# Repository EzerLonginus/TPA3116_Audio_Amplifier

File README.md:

# TPA3116_Audio_Amplifier
TPA3116 Stereo and Sub-Woofer Audio Amplifier.  D-Class 50W Stereo Amplifier.  The schematic and layout are pretty much similar to the one layout in the datasheet.  Nothing too fancy, however the Subwoofer does have a summed Left and Right channel via two 470 ohm resistors `R78 R79`. The input is assumed to be a line level stereo input through a 3.5mm jack.  However, there are some through hole pins should a different connector or input be desired.  The banana plug holes on the all the speaker ouputs are for potential convenience for swapping out speakers.  Not strictly necessary, one could solder speaker cable to those through holes, or just juse the screw terminals.  The banana plugs for the power input are there for similar reasons.  

## Schematic

## Layout

## BOM Link
1. [OCTOPART BOM](https://octopart.com/bom-tool/Kn64f8nE)

## Datasheets and External Links
1. [TPA3116](https://www.ti.com/lit/ds/symlink/tpa3116d2.pdf)

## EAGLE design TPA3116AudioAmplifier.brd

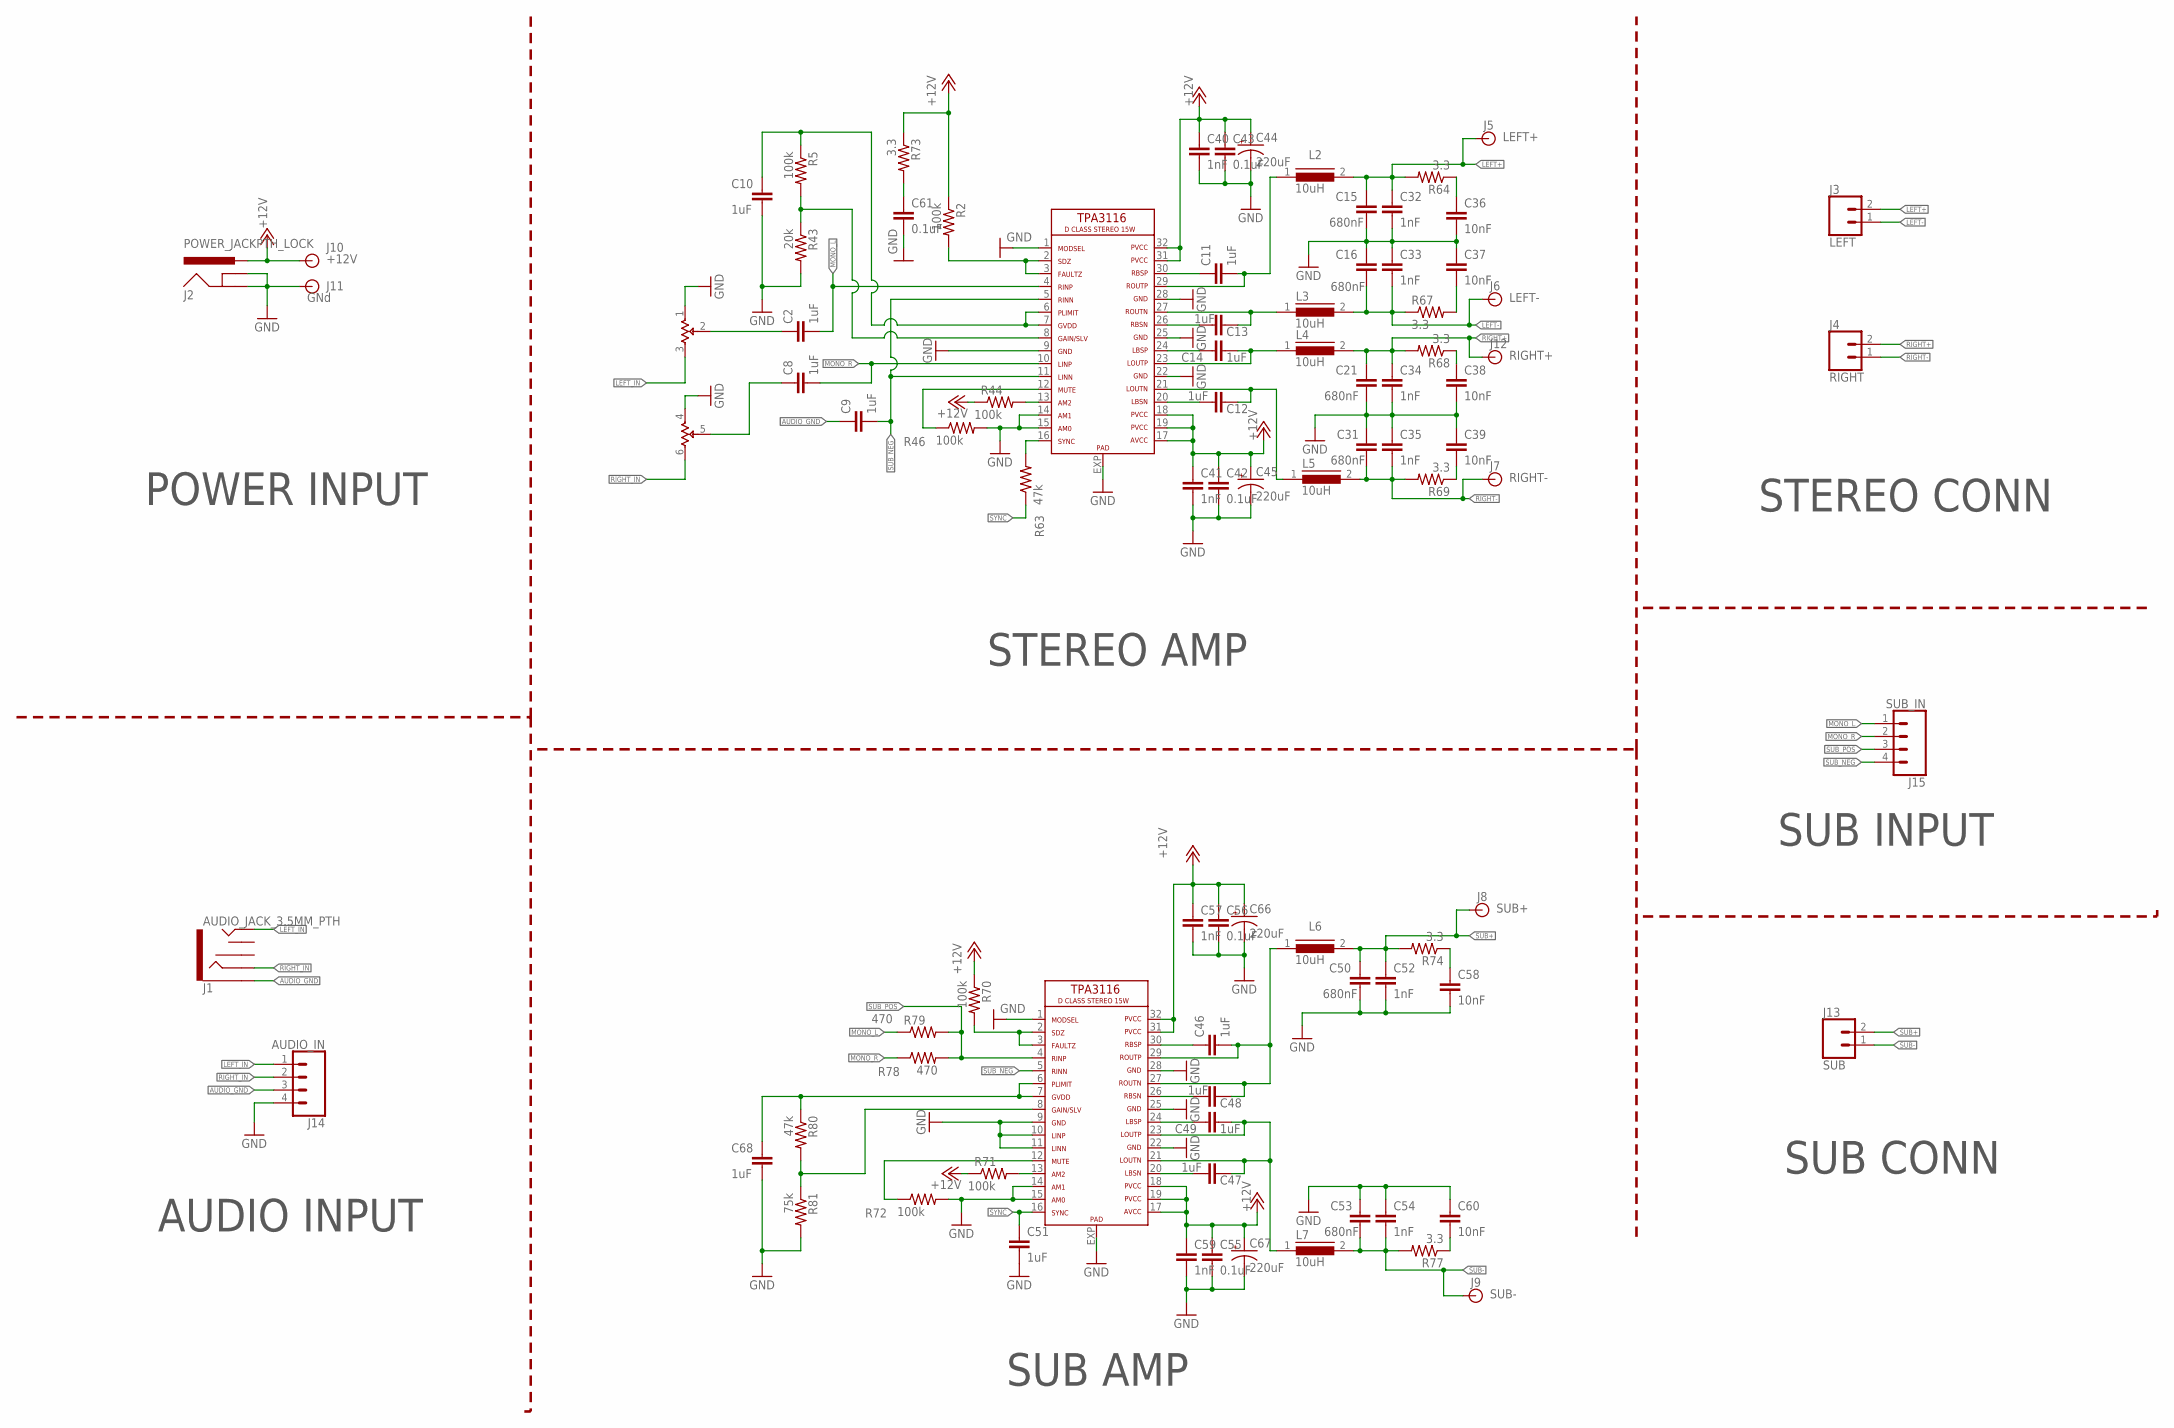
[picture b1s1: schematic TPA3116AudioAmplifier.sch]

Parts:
C2, C8, C9, C10, C11, C12, C13, C14, C46, C47, C48, C49, C51, C68: 1uF; C0603K
C15, C16, C21, C31, C50, C53: 680nF; C0805
C32, C33, C34, C35, C40, C41, C52, C54, C57, C59: 1nF; C0603K
C36, C37, C38, C39, C58, C60: 10nF; C0603K
C42, C43, C55, C56, C61: 0.1uF; C0603K
C44, C45, C66, C67: 220uF; E5-10,5
J1: AUDIO_JACK_3.5MM_PTH; AUDIO-JACK
J2: POWER_JACKPTH_LOCK; POWER_JACK_PTH_LOCK
J3: LEFT; SCREWTERMINAL-5MM-2
J4: RIGHT; SCREWTERMINAL-5MM-2
J5: LEFT+; BANANA_CONN
J6: LEFT-; BANANA_CONN
J7: RIGHT-; BANANA_CONN
J8: SUB+; BANANA_CONN
J9: SUB-; BANANA_CONN
J10: +12V; BANANA_CONN
J11: GNd; BANANA_CONN
J12: RIGHT+; BANANA_CONN
J13: SUB; SCREWTERMINAL-5MM-2
J14: AUDIO_IN; 1X04
J15: SUB_IN; 1X04
L2, L3, L4, L5, L6, L7: 10uH; DR125
R2, R5, R44, R46, R70, R71, R72: 100k; R0805
R43: 20k; R0805
R63, R80: 47k; R0805
R64, R67, R68, R69, R73, R74, R77: 3.3; M0805
R78, R79: 470; R0805
R81: 75k; R0805
U$1, U$3: TPA3116HTSSOP32; HTSSOP32DAP
U$2: DUAL_POT_H

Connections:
+12V: C40.1, C41.1, C42.1, C43.1, C44.+, C45.+, C55.1, C56.1, C57.1, C59.1, C66.+, C67.+, J2.PWR, J10.P$1, R2.1, R44.1, R70.1, R71.1, R73.1, U$1.17 (AVCC), U$1.18 (PVCC0), U$1.19 (PVCC1), U$1.31 (PVCC2), U$1.32 (PVCC3), U$3.17 (AVCC), U$3.18 (PVCC0), U$3.19 (PVCC1), U$3.31 (PVCC2), U$3.32 (PVCC3)
AUDIO_GND: C9.1, J1.SLEEVE, J14.3
GND: C10.2, C15.2, C16.1, C21.2, C31.1, C32.2, C33.1, C34.2, C35.1, C36.2, C37.1, C38.2, C39.1, C40.2, C41.2, C42.2, C43.2, C44.-, C45.-, C50.2, C51.2, C52.2, C53.1, C54.1, C55.2, C56.2, C57.2, C58.2, C59.2, C60.1, C61.2, C66.-, C67.-, C68.2, J2.GND, J2.GNDBREAK, J11.P$1, J14.4, R43.2, R46.2, R72.2, R81.2, U$1.1 (MODSEL), U$1.9 (GND0), U$1.10 (LINP), U$1.11 (LINN), U$1.14 (AM1), U$1.15 (AM0), U$1.22 (GND1), U$1.25 (GND2), U$1.28 (GND3), U$1.EXP, U$2.1, U$2.4, U$3.1 (MODSEL), U$3.9 (GND0), U$3.14 (AM1), U$3.15 (AM0), U$3.22 (GND1), U$3.25 (GND2), U$3.28 (GND3), U$3.EXP
LEFT+: C15.1, C32.1, J3.2, J5.P$1, L2.2, R64.2
LEFT-: C16.2, C33.2, J3.1, J6.P$1, L3.2, R67.1
LEFT_IN: J1.TIP, J14.1, U$2.3
LOUTN: C13.2, L3.1, U$3.27 (ROUTN)
LOUTP: C11.2, L2.1, U$3.29 (ROUTP)
MONO_L: C2.2, J15.1, R79.1, U$3.4 (RINP)
MONO_R: C8.2, J15.2, R78.1, U$3.10 (LINP)
unnamed: C8.1, U$2.5
unnamed: R70.2, U$1.2 (SDZ), U$1.3 (FAULTZ)
unnamed: C61.1, R73.2
unnamed: R2.2, U$3.2 (SDZ), U$3.3 (FAULTZ)
unnamed: R44.2, U$3.13 (AM2)
unnamed: R46.1, U$3.12 (MUTE)
unnamed: R5.2, R43.1, U$3.8 (GAIN/SLV)
unnamed: C2.1, U$2.2
unnamed: R80.2, R81.1, U$1.8 (GAIN/SLV)
unnamed: C10.1, R5.1, U$3.6 (PLIMIT), U$3.7 (GVDD)
unnamed: R63.2, U$3.16 (SYNC)
unnamed: C11.1, U$3.30 (RBSP)
unnamed: C12.1, U$3.20 (LBSN)
unnamed: C13.1, U$3.26 (RBSN)
unnamed: C14.1, U$3.24 (LBSP)
unnamed: C68.1, R80.1, U$1.6 (PLIMIT), U$1.7 (GVDD)
unnamed: R71.2, U$1.13 (AM2)
unnamed: C36.1, R64.1
unnamed: R72.1, U$1.12 (MUTE)
unnamed: C38.1, R68.1
unnamed: C37.2, R67.2
unnamed: C39.2, R69.1
unnamed: C46.1, U$1.30 (RBSP)
unnamed: C47.1, U$1.20 (LBSN)
unnamed: C48.1, U$1.26 (RBSN)
unnamed: C49.1, U$1.24 (LBSP)
unnamed: C58.1, R74.1
unnamed: C60.2, R77.1
RIGHT+: C21.1, C34.1, J4.2, J12.P$1, L4.2, R68.2
RIGHT-: C31.2, C35.2, J4.1, J7.P$1, L5.2, R69.2
RIGHT_IN: J1.RING, J14.2, U$2.6
ROUTN: C12.2, L5.1, U$3.21 (LOUTN)
ROUTP: C14.2, L4.1, U$3.23 (OUTPL)
SOUTN: C47.2, C49.2, L7.1, U$1.21 (LOUTN), U$1.23 (OUTPL)
SOUTP: C46.2, C48.2, L6.1, U$1.27 (ROUTN), U$1.29 (ROUTP)
SUB+: C50.1, C52.1, J8.P$1, J13.2, L6.2, R74.2
SUB-: C53.2, C54.2, J9.P$1, J13.1, L7.2, R77.2
SUB_NEG: C9.2, J15.4, U$1.5 (RINN), U$3.5 (RINN), U$3.11 (LINN)
SUB_POS: J15.3, R78.2, R79.2, U$1.4 (RINP)
SYNC: C51.1, R63.1, U$1.16 (SYNC)

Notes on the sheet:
SUB AMP
STEREO AMP
AUDIO INPUT
POWER INPUT
STEREO CONN
SUB INPUT
SUB CONN

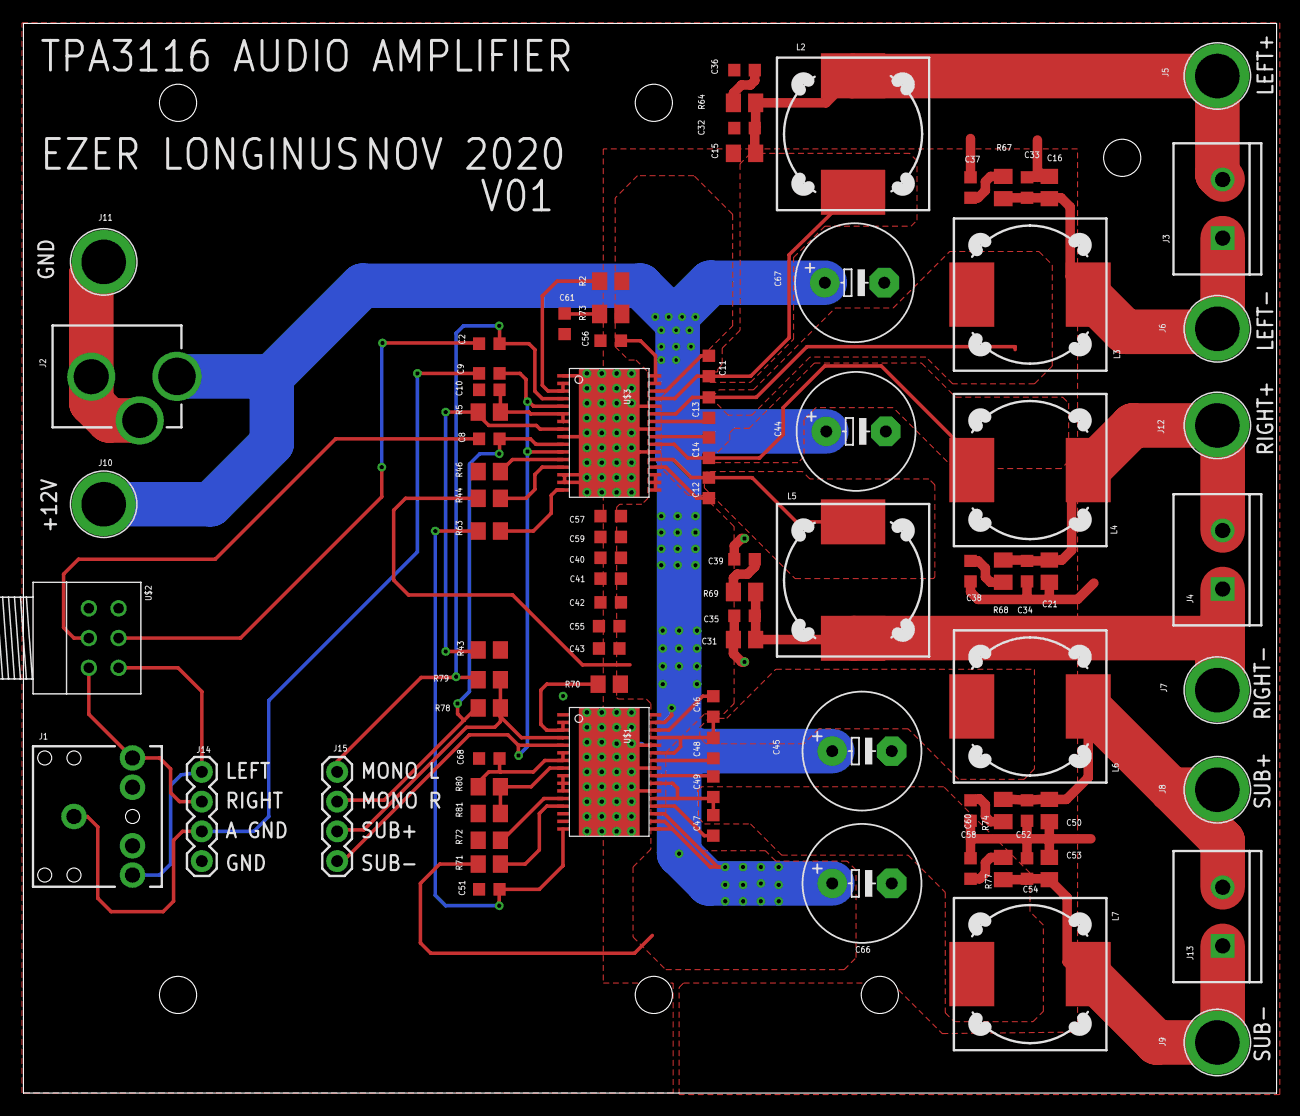
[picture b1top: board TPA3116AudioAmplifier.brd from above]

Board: 2 copper layers, 107.0 x 91.4 mm, 89 parts (0 on the bottom side), 50 nets.

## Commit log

2020-11-30 Updated README with pictures
2020-11-30 Updated README with pictures time 2
2020-11-30 Updated README with pictures again again
2020-11-30 Organized File Structure
2020-11-30 Added more (con)text to the README

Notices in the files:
parts and their libraries:
SparkFun-Connectors: Licensing: Creative Commons ShareAlike 4.0 International - https://creativecommons.org/licenses/by-sa/4.0
